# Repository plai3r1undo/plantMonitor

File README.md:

# plantMonitor

House-plant monitoring: one ESP32 per pot measures light, air temperature/humidity and soil moisture, and sends readings over WiFi to a central Rust server. The server compares them with each species' optimal ranges, sends push notifications when a plant needs attention, serves a password-protected web dashboard (where you also manage plants and species), and exposes a JSON/CSV API for scripts.

```
 ┌──────────── pot ────────────┐          ┌──────────────── DMZ host ────────────────┐
 │ BH1750  DHT22  HW-390       │HTTPS, LAN│ Caddy (TLS) ──► plant-server (Rust)      │
 │    └──── ESP32 ────┘        │ ───────► │                  SQLite · alerts · UI    │──► ntfy ──► phone
 │  wake → measure → POST →    │          └──────────────────────────────────────────┘
 │  deep sleep (10 min)        │                     ▲ browser (login) / curl (token)
 └─────────────────────────────┘
```

```
firmware/   ESP32 sensor node (C++, Arduino framework, PlatformIO)
server/     Rust server + web UI (plain HTML/CSS/JS, embedded in the binary)
deploy/     systemd unit, Caddy reverse-proxy config, install script
build.sh    builds/flashes the firmware and builds/runs the server
```

## Wiring (generic ESP32 DevKit, WROOM-32)

| Sensor          | Sensor pin | ESP32 pin |
|-----------------|------------|-----------|
| BH1750          | VCC / GND  | 3V3 / GND |
|                 | SDA        | GPIO 21   |
|                 | SCL        | GPIO 22   |
|                 | ADDR       | GND / unconnected (address 0x23) |
| DHT22           | VCC / GND  | 3V3 / GND |
|                 | DATA       | GPIO 4 (10 kΩ pull-up to 3V3 if the module has none) |
| HW-390 (soil)   | VCC / GND  | 3V3 / GND |
|                 | AOUT       | GPIO 34   |

Power the HW-390 from **3V3**, not 5 V, so its output stays inside the ESP32 ADC range. The soil sensor must be on an ADC1 pin (GPIO 32–39) because ADC2 can't be used while WiFi is on. Pins are set in `firmware/include/config.h`.

## The firmware (no C++ knowledge needed)

You normally only edit two files, both made of `#define NAME value` lines:

- `firmware/include/secrets.h`: WiFi name/password, server URL, device key
- `firmware/include/config.h`: pins and measurement interval (defaults match the wiring above)

`src/main.cpp` (~170 lines) does: read sensors → connect WiFi → POST JSON → deep sleep. Every node flashed with the same firmware reports as `plant-<last 3 MAC bytes>`.

## Quick start (testing on your LAN)

```sh
cp server/config.example.toml server/config.toml
#   edit: device_key (openssl rand -hex 24), listen = "0.0.0.0:8080", secure_cookies = false
./build.sh user-add admin        # create your login
./build.sh run-server            # http://<this-machine>:8080

./build.sh setup                 # installs PlatformIO into .tools/ (first time only)
./build.sh build                 # first run creates firmware/include/secrets.h: fill it in
./build.sh deploy -p /dev/ttyUSB0   # flash + serial monitor
```

To flash on Fedora you need to be in the `dialout` group: `sudo usermod -aG dialout $USER`, then log out and back in.

New sensors show up on the dashboard under **Unassigned devices**. Click **Add as plant**, pick the species, and calibrate the soil sensor. The plant form has **Use latest** buttons: hold the probe in dry air, wait for a reading, press *Use latest* next to *Dry*, then do the same in a glass of water for *Wet*.

Later changes, all from the **Plants** tab:

- **Recalibrate** a plant's soil sensor: a guided dialog takes the new dry and wet values. Until you save or cancel (at most 30 min), the probe's readings stay out of the plant's history and alerts.
- **Move a sensor** to another plant: edit the plant that should get it and pick the device. Readings belong to the plant they were taken in, so the old plant keeps its history (it shows *No sensor* until it gets one), and the sensor's calibration is copied along.
- **Delete an offline device** (broken or retired): it is removed from its plant, which keeps its history. If it reports again it shows up as a new device.

**Soil drying check.** From the soil moisture history, the server finds waterings (sharp rises) and measures how long the soil takes to dry down to the species' minimum. Each species has an expected drying time (*Dries in* on the Species tab). Soil that stays wet much longer (e.g. a cactus in a dense mix, or a pot without drainage) or dries much faster (mix too coarse, pot too small) gets a hint on the plant's card, with details in its chart view. It needs at least one thorough watering followed by a few days of readings, and isn't judged while a plant is dormant.

## Production: exposing it in a DMZ

### 1. Install the server

On the DMZ machine (Fedora example):

```sh
./build.sh server
sudo deploy/install.sh            # user, dirs, config with random device key, systemd unit
sudo -u plantmon plant-server -c /etc/plant-monitor/config.toml user-add <name>
sudo dnf install caddy
sudo cp deploy/Caddyfile /etc/caddy/Caddyfile   # edit: LAN name, optional public site
sudo systemctl enable --now caddy
sudo firewall-cmd --permanent --add-service=https && sudo firewall-cmd --reload
```

The server only listens on `127.0.0.1:8080`. Caddy handles HTTPS and is the only thing reachable from the network.

`deploy/Caddyfile` has two sites:

- **LAN site (required)**, e.g. `plants.home.arpa`: used by the sensors and by browsers at home. Caddy is its own certificate authority (`tls internal`), so it needs no domain and no internet. Add a DNS entry for the name on your router, or use the machine's fixed IP as the site address.
- **Public site (optional)**, e.g. `plants.example.com`: only if you want the dashboard from outside. Caddy gets a free Let's Encrypt certificate. It doesn't serve the sensor endpoint.

### 2. HTTPS for the sensors

The sensors only talk to the LAN site. They use HTTPS and verify the certificate against Caddy's root certificate, which is built into the firmware, so the device key can't be sniffed and nobody can impersonate the server:

```sh
sudo cat /var/lib/caddy/.local/share/caddy/pki/authorities/local/root.crt > firmware/root_ca.pem
```

Then set `SERVER_URL "https://plants.home.arpa"` (or `https://<fixed IP>`) and `DEVICE_KEY` (from `/etc/plant-monitor/config.toml`) in `secrets.h` and reflash. The root certificate is valid for 10 years; Caddy renews the server certificates under it by itself.

The server also refuses readings from any address outside your LAN (`device_networks` in config.toml, default: the private ranges 10/8, 172.16/12, 192.168/16 and IPv6 ULA), so even with the public site enabled, nobody on the internet can submit readings.

### 3. Firewall rules on your router

| From → To | Allow |
|---|---|
| Internet → DMZ host | nothing; only if you enable the public site: TCP 443 + 80 (80 for Let's Encrypt) |
| LAN → DMZ host | TCP 443 (sensors, browser), TCP 22 from your PC only |
| DMZ host → LAN | **nothing** (if the host is compromised, it can't reach your network) |
| DMZ host → Internet | TCP 443 (ntfy, OS updates, Let's Encrypt), DNS, NTP |

### 4. Keep the host healthy

Run the read-only check script now and then (it changes nothing):

```sh
sudo deploy/check-host.sh --lan 192.168.1.1   # IP of your router or a LAN PC
```

It checks updates, SELinux, firewall, open ports, SSH settings, accounts, the plant-server and Caddy setup, failed logins, and (with `--lan`) that the DMZ host can't connect into your LAN.

- SSH with keys only (`PasswordAuthentication no`), no root login
- Automatic security updates: `sudo dnf install dnf-automatic && sudo systemctl enable --now dnf-automatic-install.timer`
- Nothing else running on the DMZ host (disable mDNS/LLMNR: `systemctl disable --now avahi-daemon`, `LLMNR=no` and `MulticastDNS=no` in `/etc/systemd/resolved.conf`)
- Back up `/var/lib/plant-monitor/plants.db` and `/etc/plant-monitor/config.toml`
- Watch failed logins: `journalctl -u plant-server | grep "failed login"`

## Security model

What the server does:

| Threat | Protection |
|---|---|
| Password guessing | Argon2id password hashes; 5 failed logins per IP (per /64 for IPv6) and 30 overall per 15 min, then HTTP 429; unknown usernames take as long as wrong passwords |
| Stolen session / DB leak | Random 256-bit session and API tokens, stored only as SHA-256 hashes; cookie is `HttpOnly`, `Secure`, `SameSite=Strict`, `__Host-` prefixed; sessions expire (14 days); changing your password logs out every other session |
| Cross-site request forgery | `SameSite=Strict` plus a required `X-Requested-With` header on every state-changing request |
| Script injection (XSS) | Every value is HTML-escaped; strict Content-Security-Policy (no inline scripts or styles, no third-party content) |
| Clickjacking, sniffing, leaks | `frame-ancestors 'none'`, `X-Frame-Options`, `nosniff`, `no-referrer`, HSTS (via Caddy) |
| Fake sensor data | Readings accepted only from LAN addresses, with the device key (compared in constant time), sent only over verified HTTPS |
| Oversized / slow requests | 16 KB body limit, 30 s request timeout, Caddy in front |
| Server compromise | Rust (memory safe), no unsafe code, runs as an unprivileged user under systemd sandboxing with no capabilities and a read-only filesystem except its data directory; DMZ firewall blocks access to your LAN |
| SQL injection | All queries are parameterized |

What's left, honestly:

- **All sensors share one device key.** Someone with access to your LAN who takes a sensor out of a pot and reads its flash can submit fake readings, but they can't log in or read any data. You can rotate the key in config.toml and reflash.
- **The global login limit can be used to lock you out** by an attacker who keeps failing logins. Sessions last 14 days, so this only blocks *new* logins, and the attacker still can't get in.
- **No two-factor authentication.** Use a long, unique password (a password manager).
- **Dependencies** (axum, rusqlite, etc.) can have vulnerabilities. Rebuild and redeploy now and then (`cargo update && ./build.sh server && sudo deploy/install.sh`); `cargo install cargo-audit && cargo audit` checks for known issues.
- If only you need remote access, a **VPN (WireGuard)** into your network is still safer than any exposed web app. Everything here works the same over a VPN.

## Notifications (ntfy)

[ntfy.sh](https://ntfy.sh) is free and needs no account. Install the ntfy app on your phone and subscribe to a long random topic name, then add it to the config:

```toml
public_url = "https://plants.example.com"   # where tapping the notification goes

[ntfy]
server = "https://ntfy.sh"
topic = "plants-3f9c0e1a7b2d4c86e5a1"         # "plants-" + openssl rand -hex 10
```

On the public server, anyone who knows the topic name can read it, so treat the name like a password. You can also self-host ntfy and set `token`. A problem is notified after it has lasted `alert_after_minutes` (default 30), repeated every `remind_after_hours` (default 24), and you get a ✅ when it's fixed. Alerts can be turned off per plant. **Settings → Send test notification** checks the setup.

## How plants are evaluated

Temperature, humidity and soil moisture use the latest reading. Light uses the **average lux over the last 24 h, counting only readings ≥ 50 lx**, so night readings don't flag every plant as too dark. A plant's status is `ok`, `attention` (something out of range; the UI shows advice), `offline` (no reading for `offline_after_minutes`), `no_data`, or `no_sensor` (its sensor was moved or deleted).

## API

Create a read-only token under **Settings → API tokens**, then:

```sh
T=your-token; S=https://plants.example.com
curl -s -H "Authorization: Bearer $T" $S/api/plants | jq -r '.[] | "\(.name): \(.status)"'
curl -s -H "Authorization: Bearer $T" "$S/api/plants/1/readings?hours=168&format=csv" > week.csv
```

| Method | Path | Description |
|---|---|---|
| GET  | `/api/plants` | All plants with latest reading, checks and status |
| GET  | `/api/plants/{id}` | One plant |
| GET  | `/api/plants/{id}/readings?hours=24&format=json\|csv` | History (max 1 year) |
| GET  | `/api/species` | Species and their optimal ranges |
| GET  | `/api/devices` | Sensors that are assigned or have unassigned readings, with `online` |
| GET  | `/api/health` | Liveness check (no auth) |

Tokens are read-only. Creating, editing and deleting (plants, species, tokens) needs a logged-in browser session.

## Server CLI

```sh
plant-server -c config.toml user-add NAME      # create a login (prompts for password, min 12 chars; shorter only after confirming, and the UI then warns until it is changed)
plant-server -c config.toml user-passwd NAME   # reset a password, ends all its sessions
plant-server -c config.toml user-del NAME
plant-server -c config.toml user-list
```

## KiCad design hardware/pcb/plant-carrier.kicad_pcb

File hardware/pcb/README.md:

# Sensor carrier board

A 72 × 62 mm two-layer board that holds one sensor node. Everything plugs in, so any part can be swapped:

- **ESP32 DevKit V1 (30 pin)** plugs into two 15-pin female sockets.
- **BH1750 (GY-302)**, top right: two parallel rows, use one. The upper row (J3) takes a 5-pin socket or header; the lower row (J7) is solder holes for wires (1.0 mm, fits 22–24 AWG), to place the light sensor elsewhere.
- **DHT22 module (3 pin)** plugs into a 3-pin female socket, bottom right. A slot in the board keeps the ESP32's heat away from it.
- **HW-390 soil sensor** connects to a 3-pin header (for the sensor's cable) **or** to 3 solder holes (for wires soldered directly). Use one or the other.

The copper follows the firmware's pins: DHT22 → D4, SDA → D21, SCL → D22, soil → D34, plus 3V3 and GND. The BH1750's ADDR pin is tied to GND (I²C address 0x23). There is no copper under the ESP32 antenna.

## Check before ordering

The board matches these parts (confirmed against the real modules). If you use a different module, check it first:

| Part | Board expects |
|---|---|
| ESP32 DevKit V1, 30 pin | Pin rows **25.4 mm** apart (`ROW_SPACING` in `generate_pcb.py`). Antenna up: left EN…VIN, right D23…3V3 (D17/D16 are also called TX2/RX2). |
| DHT22 module | **DAT VCC GND**, left to right |
| BH1750 (GY-302) | **VCC SCL SDA GND ADDR** (SDA may be printed as DAT) |
| HW-390 soil sensor | **AOUT VCC GND** (A V G on the board) |

Each module lies flat above the board. Plug it in so its pin labels match the board's; depending on the module, it may stick out over the board's edge.

## Ordering (JLCPCB, PCBWay, …)

Upload `plant-carrier-gerbers.zip`. The defaults are fine:

| Setting | Value |
|---|---|
| Layers | 2 |
| Thickness | 1.6 mm |
| Min track / clearance | 0.4 mm / 0.2 mm (any standard service) |
| Holes | 1.0 mm plated, 3.2 mm non-plated (M3) |
| Surface finish | HASL (lead-free if you prefer) |

The board contains one internal slot (1.5 × 16 mm); the fab mills it automatically from the Edge.Cuts layer.

## Parts to solder

| Ref | Part | Qty |
|---|---|---|
| J1, J2 | Female pin socket 1×15, 2.54 mm | 2 |
| J3 | Female pin socket 1×5, 2.54 mm (BH1750 plugged in), **or** solder 5 wires into J7 | 1 |
| J4 | Female pin socket 1×3, 2.54 mm | 1 |
| J5 | Male pin header 1×3, 2.54 mm (soil cable), **or** solder wires into J6 | 1 |
| H1–H4 | M3 spacers/standoffs (optional) | 4 |

Break the sockets from long female header strips. A tip for straight sockets: plug them onto the ESP32's pins first, put the whole thing into the board, then solder. The sockets then line up exactly.

## Regenerating

The board is generated from `generate_pcb.py` (KiCad 9 Python API). After a change:

```sh
cd hardware/pcb
python3 generate_pcb.py
kicad-cli pcb drc --severity-all -o drc.rpt plant-carrier.kicad_pcb   # expect 0 errors, 0 unconnected
kicad-cli pcb render --side top -o render/top.png plant-carrier.kicad_pcb
rm -rf fab && mkdir fab
kicad-cli pcb export gerbers --layers F.Cu,B.Cu,F.Mask,B.Mask,F.Silkscreen,B.Silkscreen,F.Paste,Edge.Cuts --no-protel-ext -o fab/ plant-carrier.kicad_pcb
kicad-cli pcb export drill --excellon-separate-th -o fab/ plant-carrier.kicad_pcb
(cd fab && rm -f ../plant-carrier-gerbers.zip && zip -q ../plant-carrier-gerbers.zip *)
```

The DRC reports two expected warnings: the soil header and solder holes (J5/J6) and the light sensor socket and solder holes (J3/J7) have overlapping courtyards, because only one of each pair is used.

You can also open `plant-carrier.kicad_pcb` in KiCad and edit it by hand. The script overwrites it the next time it runs, though.

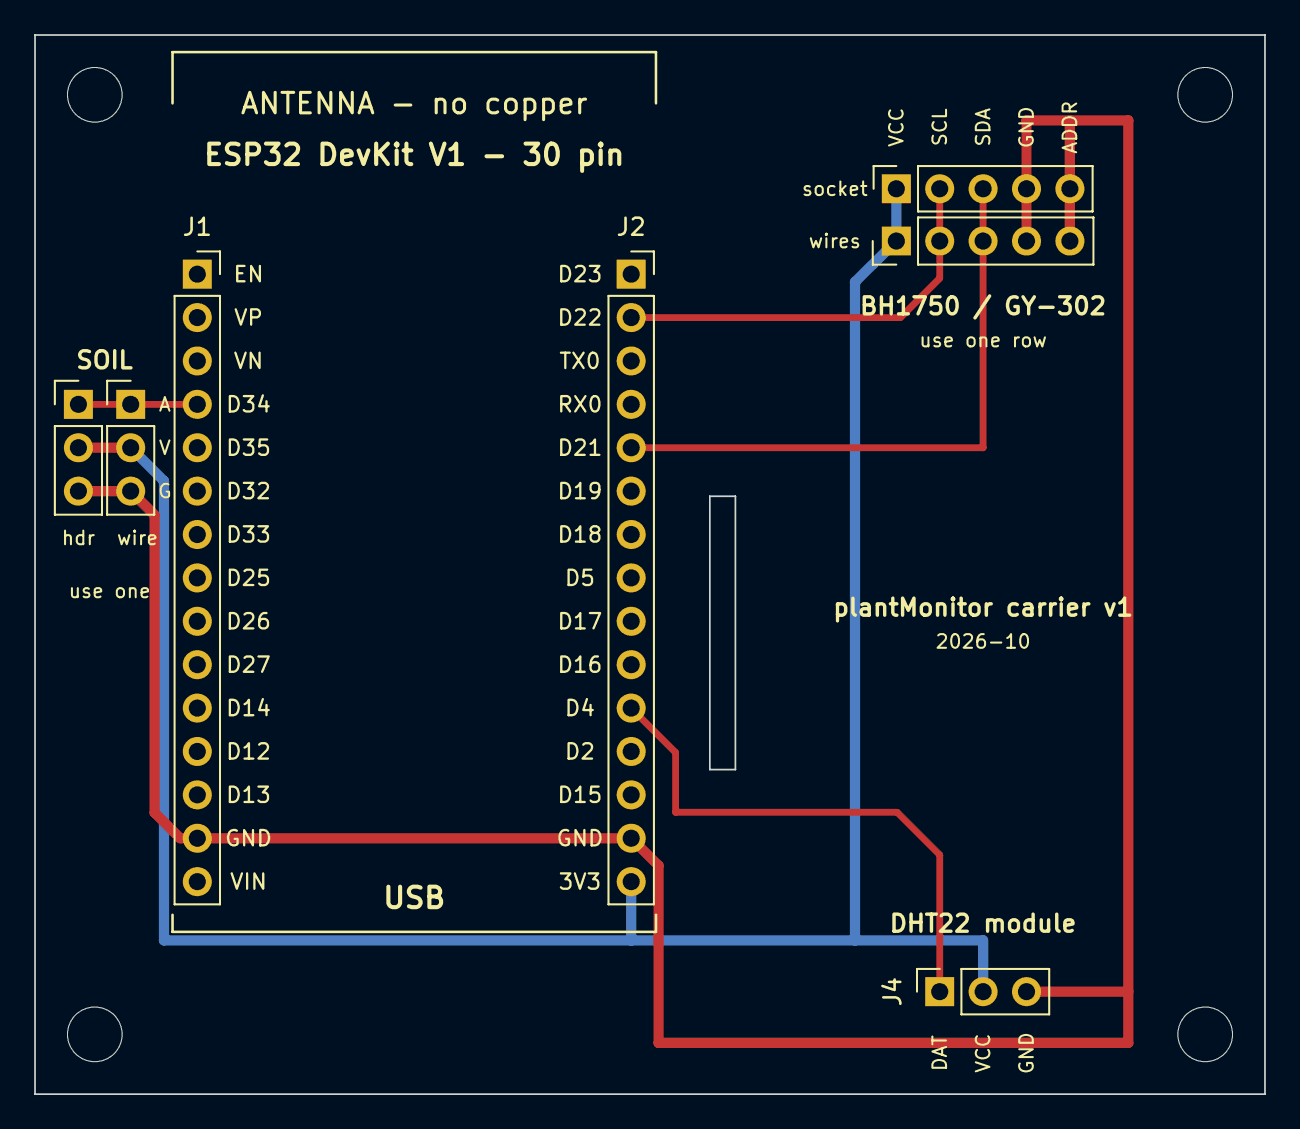
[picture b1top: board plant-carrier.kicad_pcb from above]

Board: 2 copper layers, 72.0 x 62.0 mm, 11 parts (0 on the bottom side), 6 nets.

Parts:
H1, H2, H3, H4: M3; MountingHole_3.2mm_M3
J1: ESP32 left; PinSocket_1x15_P2.54mm_Vertical
J2: ESP32 right; PinSocket_1x15_P2.54mm_Vertical
J3: BH1750 (GY-302); PinSocket_1x05_P2.54mm_Vertical
J4: DHT22 module; PinSocket_1x03_P2.54mm_Vertical
J5: Soil header; PinHeader_1x03_P2.54mm_Vertical
J6: Soil solder holes; PinHeader_1x03_P2.54mm_Vertical
J7: BH1750 solder holes; PinHeader_1x05_P2.54mm_Vertical

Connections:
+3V3: J2.15, J3.1, J4.2, J5.2, J6.2, J7.1
DHT_DATA: J2.11, J4.1
GND: J1.14, J2.14, J3.4, J3.5, J4.3, J5.3, J6.3, J7.4, J7.5
SCL: J2.2, J3.2, J7.2
SDA: J2.5, J3.3, J7.3
SOIL: J1.4, J5.1, J6.1
